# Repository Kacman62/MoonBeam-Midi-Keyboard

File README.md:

# MoonBeam Synthesizer
A standalone DAWLESS synthesizer based on a Raspberry Pi Pico. Includes a custom circuit board and codebase with the Mozzi Audio Library

# Features

- 25 multiplexed piano style keys
- Support for up to 5 notes at the same time
- 3 Analog sliders for volume pitch and vibrato
- OLED display and 2 rotary encoders with a custom code base
- Sound synthesis using the Mozzi audio library
- 4 different wave forms
- Custom ADSR editing
- Oscilloscope style waveform viewer
- Toggleable speaker and headphone out
- And more planned features for the future!

# Initial Idea
After reading the guide from Hack club and others online to make a MIDI keyboard, it seemed like a great idea. After more research though I wanted a standalone synthesizer that does not need a computer and couldn't find many examples online. This seemed like it would be easy enough so I decided to do it myself

# Schematic and Board
The whole project is built around a raspberry pi pico 1 (a pico 2 should work too but untested). A 5x5 multiplexed array of key cap switches serve as the main input. 
On the Audio side, a PCM5100 I2S DAC is channeled into a LM4810 and LM4861 audio amplifiers, that go to a speaker and headphone jack.

The PCB was a lot more challenging, just due to the sheer size of it. It ends up being about 350mm x 90mm. But the routing wasn't too hard and I like the look of how it turned out

# Case Design
There is an included case. Currently I have not received the board so I can not confirm if it works perfectly, but I designed it around the 3D cad of the board so it should work fine. 
Only 1 of each file needs to be printed and it is assembled using M4 hardware

# Software
I initially dreaded the software but it ended up being very fun after the initial hurdles. The code is split into 2 cores, 1 for audio and 1 for the digital UI. It should work with the final assembly, all the digital has been tested, but the audio is using I2S which I can't test currently. I did use it a little bit with PWM audio and that worked fine. The waveform viewer also does show an audio signal so Im pretty confident that it will work

# UI
You navigate the UI with both rotary encoders. Double clicking either brings you into the main menu. Rotate either to select an app.
* Settings (Wrench): View current notes on each audio voice and the values of the slide potentiometers
* ADSR Editor (Envelope): Use one dial to change the level of the ADSR and the other to change the time. Changing the level of the decay, sustain and release will change the other two with it. this is intended to avoid weird audio clipping
* Wave Viewer (Wave): View the current outputted wave form. Automatically adjusts the zoom if multiple voices are playing
* Wave Changer (Square Wave): Choose from either a sin, triangle, saw, or square wave

# Art
All pixel art was created by me using Aseprite. The PK Industries and the Moonbeam synth logo are unregistered trademarks, not real companies and products, and have no legal binding on anything. I am not a lawyer, and this joke has gone on too long.

# Disclaimers
If you want to know more about the design and build process check out the journal

This project is sponsored by and made in collaboration with Hack Club, go check them out

Consider this project untested. I have put my full effort into this project and fully believe that it will work, but I have not received boards yet and thus do not know if this will work first try

# Hack Club Stuff

Estimate Total Hours: 48

My Final Total: 60.31

Your Final Total: 96.73

https://blueprint.hackclub.com/projects/928 

# Update 11/11

Huge thanks to Hack Club and the Blueprint program for assisting in this project. I have now received funding for the project and will be ordering parts. Expect future updates at the start of December

# Known issues
In settings, the note played is incorrect (going to wait for boards to arrive so I can assign keys different notes)

In Wave changer, the picture of the sawtooth wave is reversed from what is seen in the wave viewer

In Wave Viewer, the wave slides around randomly. (The wave is still representative of what the audio out looks like, it's just hard to focus on it)

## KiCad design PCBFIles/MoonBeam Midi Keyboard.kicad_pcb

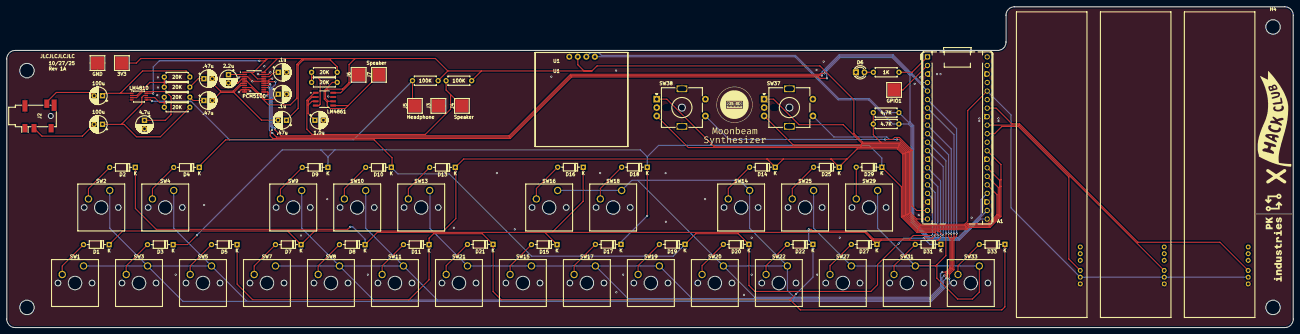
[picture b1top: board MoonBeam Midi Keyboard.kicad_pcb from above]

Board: 2 copper layers, 383.0 x 95.5 mm, 95 parts (0 on the bottom side), 76 nets.

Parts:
1.0u: 1.0u; CP_Radial_D5.0mm_P2.50mm
1K: 1k; R_Axial_DIN0207_L6.3mm_D2.5mm_P7.62mm_Horizontal
2.2u: 2.2u; CP_Radial_D5.0mm_P2.50mm
3V3: Conn_01x01_Pin; TestPoint_Pad_4.0x4.0mm
4.7K, 4.7K#2: 4.7k; R_Axial_DIN0207_L6.3mm_D2.5mm_P7.62mm_Horizontal
4.7u: 4.7u; CP_Radial_D5.0mm_P2.50mm
20K, 20K#2, 20K#3, 20K#4, 20K#5, 20K#6: 20k; R_Axial_DIN0207_L6.3mm_D2.5mm_P7.62mm_Horizontal
100K, 100K#2: 100k; R_Axial_DIN0207_L6.3mm_D2.5mm_P7.62mm_Horizontal
100u, 100u#2: 100u; CP_Radial_D5.0mm_P2.50mm
.1u, .1u#2: .1; CP_Radial_D5.0mm_P2.50mm
.47u, .47u#2, .47u#3: .47u; CP_Radial_D5.0mm_P2.50mm
A1: RaspberryPi_Pico; RaspberryPi_Pico_Common_THT
D1, D2, D3, D4, D5, D7, D8, D9, D10, D11, D13, D14, D15, D16, D17, D18, D19, D20, D21, D22, D25, D27, D29, D31, D33: D; D_DO-35_SOD27_P7.62mm_Horizontal
D6: LED; LED_D3.0mm
GND: Conn_01x01_Pin; TestPoint_Pad_4.0x4.0mm
GPIO1: Conn_01x01_Pin; TestPoint_Pad_4.0x4.0mm
H1, H2, H3, H4: MountingHole; MountingHole_4.3mm_M4
J2: AudioJack4_SwitchTR1; Jack_3.5mm_PJ31060-I_Horizontal
J3, J4, J5, J6, J7: Conn_01x01_Pin; TestPoint_Pad_4.0x4.0mm
LM4810: LM4810; TSSOP-8_3x3mm_P0.65mm
LM4861: LM4861; SOIC127P600X175-8N
PCM5100: PCM5100; TSSOP-20_4.4x6.5mm_P0.65mm
RV1, RV2, RV3: R_Potentiometer; Slide Pot
SW1, SW2, SW3, SW4, SW5, SW7, SW8, SW9, SW10, SW11, SW13, SW14, SW15, SW16, SW17, SW18, SW19, SW20, SW21, SW22, SW25, SW27, SW29, SW31, SW33: SW_Omron_B3FS; SW_Cherry_MX_1.00u_PCB
SW37, SW38: RotaryEncoder_Switch_MP; RotaryEncoder_Alps_EC11E-Switch_Vertical_H20mm_MountingHoles
U1: 0.96 OLED I2C

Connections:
1A: A1.25 (GPIO19), SW37.A
1B: A1.26 (GPIO20), SW37.B
2A: A1.27 (GPIO21), SW38.A
2B: A1.29 (GPIO22), SW38.B
+3V3: 3V3.1, 4.7K.1, 4.7K#2.1, 100K.2, 100K#2.2, A1.36 (3V3), LM4810.8 (VDD), LM4861.6 (VDD), PCM5100.1 (CPVDD), PCM5100.8 (AVDD), PCM5100.17 (XSMT), PCM5100.20 (DVDD), RV1.1, RV2.1, RV3.1, U1.2 (VCC)
BCLK: A1.4 (GPIO2), PCM5100.13 (BCK)
Col0: A1.12 (GPIO9), D1.1 (K), D7.1 (K), D13.1 (K), D14.1 (K), D25.1 (K)
Col1: A1.14 (GPIO10), D2.1 (K), D8.1 (K), D15.1 (K), D16.1 (K), D27.1 (K)
Col2: A1.15 (GPIO11), D3.1 (K), D9.1 (K), D17.1 (K), D18.1 (K), D29.1 (K)
Col3: A1.16 (GPIO12), D4.1 (K), D10.1 (K), D19.1 (K), D20.1 (K), D31.1 (K)
Col4: A1.17 (GPIO13), D5.1 (K), D11.1 (K), D21.1 (K), D22.1 (K), D33.1 (K)
DIN: A1.24 (GPIO18), PCM5100.14 (DIN)
GND: 1.0u.2, 4.7u.2, .1u.2, .1u#2.2, A1.3 (GND), A1.8 (GND), A1.13 (GND), A1.18 (GND), A1.23 (GND), A1.28 (GND), A1.33 (AGND), A1.38 (GND), D6.1 (K), GND.1, J2.R2, J3.1, LM4810.4 (GND), LM4861.7 (GND), PCM5100.3 (CPGND), PCM5100.9 (AGND), PCM5100.10 (DEMP), PCM5100.11 (FLT), PCM5100.16 (FMT), PCM5100.19 (DGND), RV1.3, RV2.3, RV3.3, SW37.C, SW37.MP, SW37.S2, SW38.C, SW38.MP, SW38.S2, U1.1 (GND)
LRCK: A1.5 (GPIO3), PCM5100.15 (LRCK)
unnamed: 1K.1, A1.1 (GPIO0)
unnamed: A1.2 (GPIO1), GPIO1.1
unnamed: 100u.2, J2.T
unnamed: 100u#2.2, J2.R1
unnamed: 20K.1, .47u.1
unnamed: 20K#2.1, .47u#2.1
unnamed: 20K#4.1, .47u#3.1
unnamed: D1.2 (A), SW1.2
unnamed: D2.2 (A), SW2.2
unnamed: D3.2 (A), SW3.2
unnamed: D4.2 (A), SW4.2
unnamed: D5.2 (A), SW5.2
unnamed: 1K.2, D6.2 (A)
unnamed: D7.2 (A), SW7.2
unnamed: D8.2 (A), SW8.2
unnamed: D9.2 (A), SW9.2
unnamed: D10.2 (A), SW10.2
unnamed: D11.2 (A), SW11.2
unnamed: D13.2 (A), SW13.2
unnamed: D14.2 (A), SW14.2
unnamed: D15.2 (A), SW15.2
unnamed: D16.2 (A), SW16.2
unnamed: D17.2 (A), SW17.2
unnamed: D18.2 (A), SW18.2
unnamed: D19.2 (A), SW19.2
unnamed: D20.2 (A), SW20.2
unnamed: D21.2 (A), SW21.2
unnamed: D22.2 (A), SW22.2
unnamed: D25.2 (A), SW25.2
unnamed: D27.2 (A), SW27.2
unnamed: D29.2 (A), SW29.2
unnamed: D31.2 (A), SW31.2
unnamed: D33.2 (A), SW33.2
unnamed: 100K.1, J4.1, LM4861.1 (SHUTDOWN)
unnamed: 100K#2.1, J5.1, LM4810.5 (SHDN)
unnamed: J6.1, LM4861.8 (V02)
unnamed: 20K#5.2, J7.1, LM4861.5 (V01)
unnamed: 2.2u.2, PCM5100.4 (CAPM)
unnamed: 2.2u.1, PCM5100.2 (CAPP)
unnamed: .1u.1, PCM5100.18 (LDOO)
unnamed: .47u.2, PCM5100.6 (OUTL)
unnamed: .47u#2.2, .47u#3.2, PCM5100.7 (OUTR)
unnamed: .1u#2.1, PCM5100.5 (VNEG)
unnamed: 4.7u.1, LM4810.3 (BYPASS)
unnamed: 20K.2, 20K#6.1, LM4810.2 (VIN1)
unnamed: 20K#2.2, 20K#3.1, LM4810.6 (VIN2)
unnamed: 20K#6.2, 100u.1, LM4810.1 (VOUT1)
unnamed: 20K#3.2, 100u#2.1, LM4810.7 (VOUT2)
unnamed: 1.0u.1, LM4861.2 (BYPASS), LM4861.3 (+IN)
unnamed: 20K#4.2, 20K#5.1, LM4861.4 (-IN)
Pot0: A1.31 (GPIO26_ADC0), RV1.2
Pot1: A1.32 (GPIO27_ADC1), RV2.2
Pot2: A1.34 (GPIO28_ADC2), RV3.2
RBut1: A1.20 (GPIO15), SW37.S1
RBut2: A1.19 (GPIO14), SW38.S1
Row0: A1.6 (GPIO4), SW1.1, SW2.1, SW3.1, SW4.1, SW5.1
Row1: A1.7 (GPIO5), SW7.1, SW8.1, SW9.1, SW10.1, SW11.1
Row2: A1.9 (GPIO6), SW13.1, SW15.1, SW17.1, SW19.1, SW21.1
Row3: A1.10 (GPIO7), SW14.1, SW16.1, SW18.1, SW20.1, SW22.1
Row4: A1.11 (GPIO8), SW25.1, SW27.1, SW29.1, SW31.1, SW33.1
SCL: 4.7K#2.2, A1.22 (GPIO17), U1.3 (SCL)
SDA: 4.7K.2, A1.21 (GPIO16), U1.4 (SDA)

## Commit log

2025-11-04 Enhance README with project details and features
    Expanded README with detailed features, design, and known issues.
2025-11-04 Update README with features and initial idea
    Expanded features section and added initial idea explanation.
2025-11-04 Refactor README.md for clarity and corrections
    Removed extra line breaks and corrected typos.
2025-11-04 Rename platformio.ini to CodeFolder/platformio.ini
2025-11-04 Add MoonBeam Midi Keyboard PCB file
2025-11-04 Rename MoonBeam Midi Keyboard.kicad_pcb to MoonBeam Midi Keyboard.kicad_pcb
2025-11-04 Fix file path typo in PCBFiles directory
2025-11-04 Rename MoonBeam Midi Keyboard.kicad_pro to MoonBeam Midi Keyboard.kicad_pro
2025-11-05 Add promo image to README
    Added a promotional image for the MoonBeam Synth.
2025-11-05 Correct formatting and typos in README.md
    Fixed formatting issues and typos in the README.
2025-11-05 Fix typos and enhance readability in README
    Corrected typos and improved clarity in README.
2025-11-05 Add promotional image to README
    Added an additional promotional image to the README.
2025-11-05 Remove extra image tag from README
    Removed an unnecessary image tag from the README.
2025-11-05 Rename image.png to CadImage.png
2025-11-05 Rename Screenshot 2025-11-04 181659.png to PCB .png
2025-11-05 Rename PCB .png to PCB.png
2025-11-05 Rename Screenshot 2025-11-04 181901.png to PixelArt.png
2025-11-05 Add PCB routing image to README
    Added an image to the README for PCB routing visualization.
2025-11-05 Change PCB image in README
    Updated PCB image link in README.md.
2025-11-05 Include CAD image in README
    Added an image of the CAD design for the case.
2025-11-05 Add pixel art image to README
    Added an image showing the pixel art for the project.
2025-11-05 Update README with Hack Club project hours
    Added estimated and final total hours for project.
2025-11-05 Add project link to README
2025-11-05 Update final total hours in README
2025-11-05 Rename project to 'MoonBeam Synthesizer'
    Updated project title and description in README.
2025-11-05 Update estimated hours and final totals in README
2025-11-05 Rename image.png to OLEDUI.png
